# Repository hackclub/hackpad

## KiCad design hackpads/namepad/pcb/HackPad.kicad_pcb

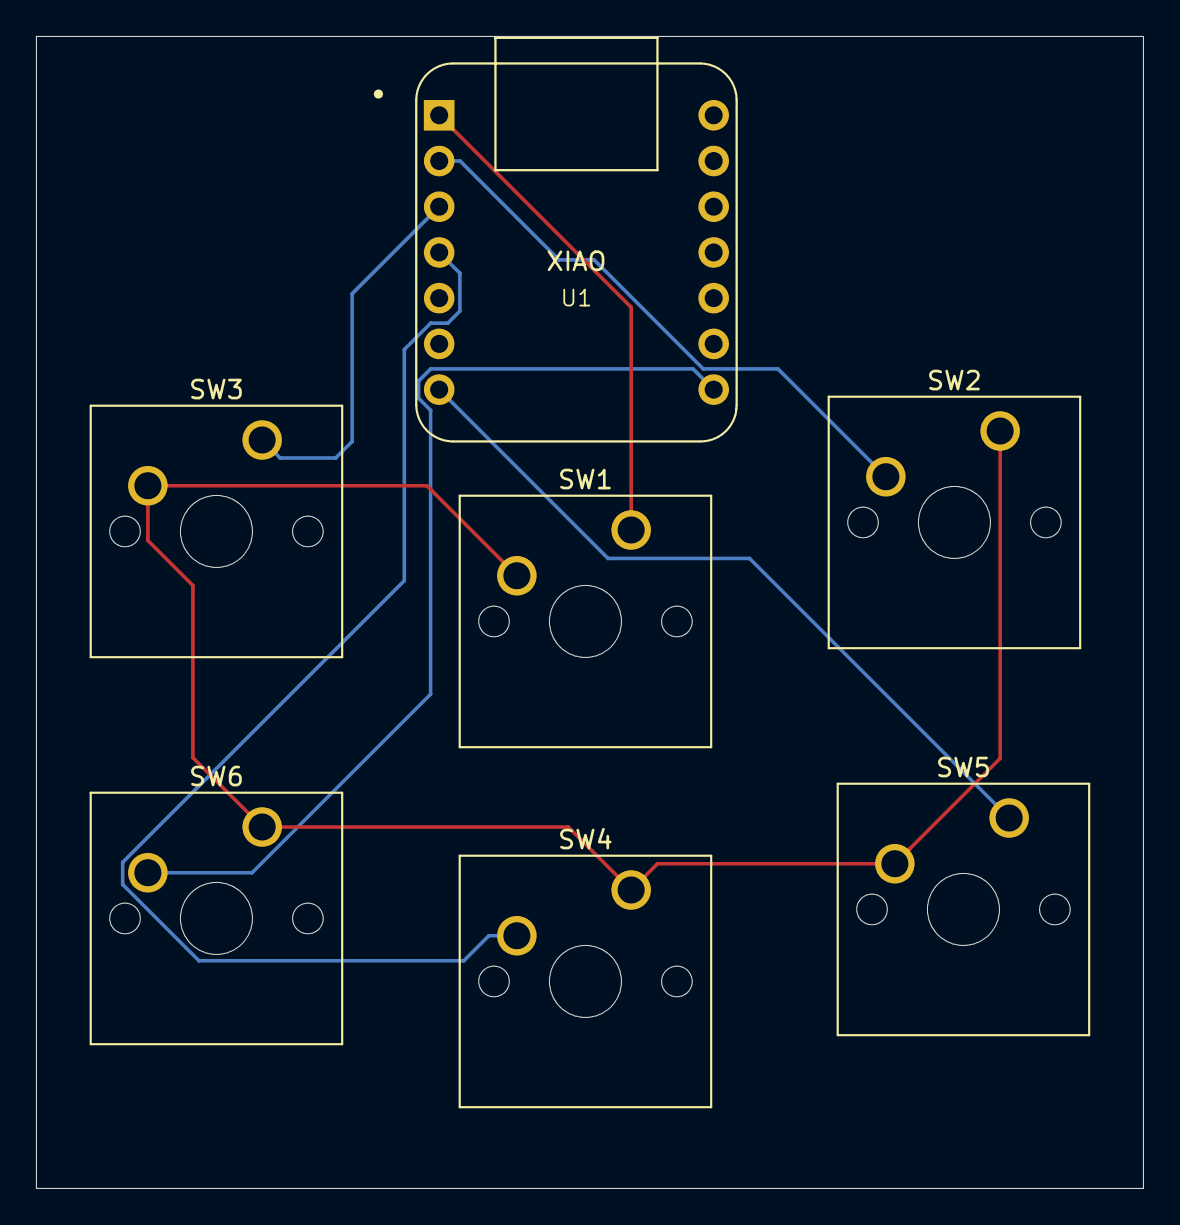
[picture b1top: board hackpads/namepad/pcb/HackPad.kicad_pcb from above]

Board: 2 copper layers, 61.5 x 64.0 mm, 7 parts (0 on the bottom side), 7 nets.

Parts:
SW1, SW2, SW3, SW4, SW5, SW6: SW_Push; SW_Cherry_MX_1.00u_PCB
U1: Seeed Studio XIAO SAMD21; XIAO-Generic-Thruhole-14P-2.54-21X17.8MM

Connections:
GND: SW1.2, SW2.1, SW3.2, SW4.1, SW5.2, SW6.1
SW1: SW1.1, U1.1 (PA02_A0_D0)
SW2: SW2.2, U1.2 (PA4_A1_D1)
SW3: SW3.1, U1.3 (PA10_A2_D2)
SW4: SW4.2, U1.4 (PA11_A3_D3)
SW5: SW5.1, U1.7 (PB08_A6_D6_TX)
SW6: SW6.2, U1.8 (PB09_A7_D7_RX)

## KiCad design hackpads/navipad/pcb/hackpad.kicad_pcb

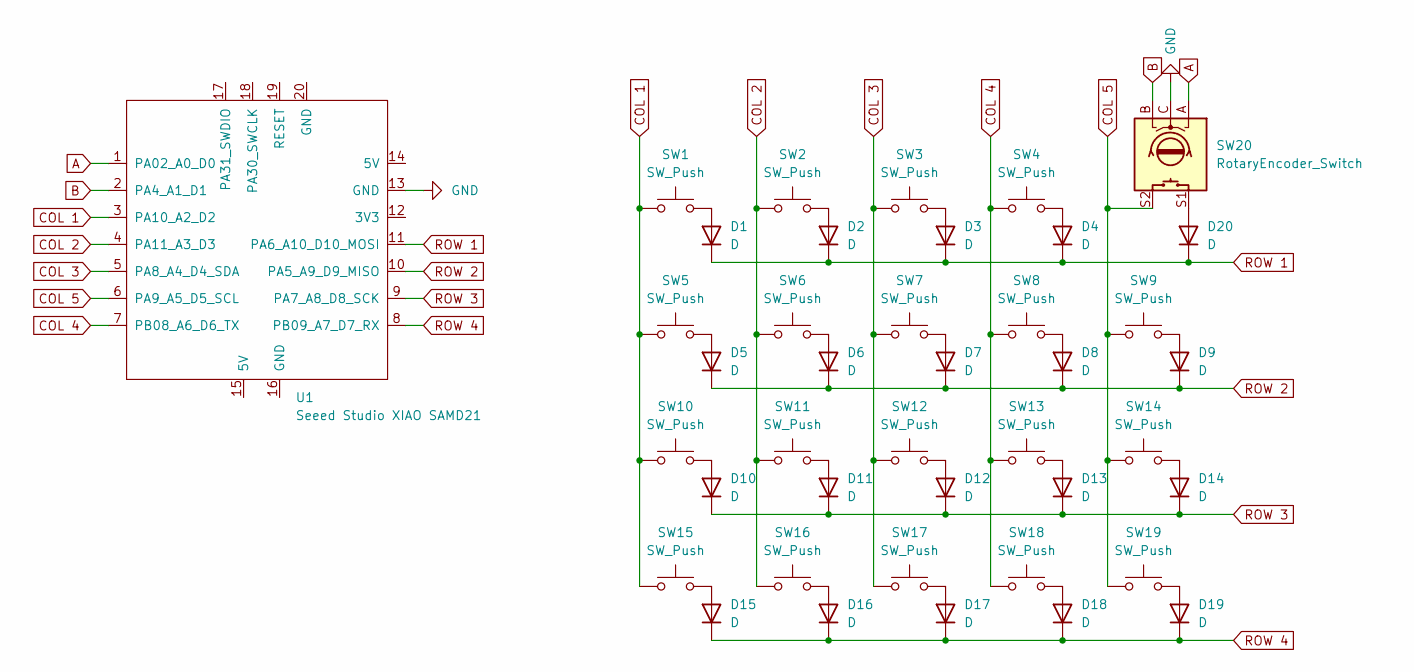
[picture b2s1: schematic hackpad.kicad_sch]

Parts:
D1, D2, D3, D4, D5, D6, D7, D8, D9, D10, D11, D12, D13, D14, D15, D16, D17, D18, D19, D20: D; D_DO-35_SOD27_P7.62mm_Horizontal
SW1, SW2, SW3, SW4, SW5, SW6, SW7, SW8, SW9, SW10, SW11, SW12, SW13, SW14, SW15, SW16, SW17, SW18, SW19: SW_Push; SW_Cherry_MX_1.00u_PCB_3D
SW20: RotaryEncoder_Switch; RotaryEncoder_Alps_EC11E-Switch_Vertical_H20mm_3D
U1: Seeed Studio XIAO SAMD21; XIAO-Generic-Thruhole-14P-2.54-21X17.8MM_3D

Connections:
A: SW20.A, U1.1 (PA02_A0_D0)
B: SW20.B, U1.2 (PA4_A1_D1)
COL 1: SW1.1, SW5.1, SW10.1, SW15.1, U1.3 (PA10_A2_D2)
COL 2: SW2.1, SW6.1, SW11.1, SW16.1, U1.4 (PA11_A3_D3)
COL 3: SW3.1, SW7.1, SW12.1, SW17.1, U1.5 (PA8_A4_D4_SDA)
COL 4: SW4.1, SW8.1, SW13.1, SW18.1, U1.7 (PB08_A6_D6_TX)
COL 5: SW9.1, SW14.1, SW19.1, SW20.S2, U1.6 (PA9_A5_D5_SCL)
GND: SW20.C, U1.13 (GND)
unnamed: D1.2 (A), SW1.2
unnamed: D2.2 (A), SW2.2
unnamed: D3.2 (A), SW3.2
unnamed: D4.2 (A), SW4.2
unnamed: D5.2 (A), SW5.2
unnamed: D6.2 (A), SW6.2
unnamed: D7.2 (A), SW7.2
unnamed: D8.2 (A), SW8.2
unnamed: D9.2 (A), SW9.2
unnamed: D10.2 (A), SW10.2
unnamed: D11.2 (A), SW11.2
unnamed: D12.2 (A), SW12.2
unnamed: D13.2 (A), SW13.2
unnamed: D14.2 (A), SW14.2
unnamed: D15.2 (A), SW15.2
unnamed: D16.2 (A), SW16.2
unnamed: D17.2 (A), SW17.2
unnamed: D18.2 (A), SW18.2
unnamed: D19.2 (A), SW19.2
unnamed: D20.2 (A), SW20.S1
ROW 1: D1.1 (K), D2.1 (K), D3.1 (K), D4.1 (K), D20.1 (K), U1.11 (PA6_A10_D10_MOSI)
ROW 2: D5.1 (K), D6.1 (K), D7.1 (K), D8.1 (K), D9.1 (K), U1.10 (PA5_A9_D9_MISO)
ROW 3: D10.1 (K), D11.1 (K), D12.1 (K), D13.1 (K), D14.1 (K), U1.9 (PA7_A8_D8_SCK)
ROW 4: D15.1 (K), D16.1 (K), D17.1 (K), D18.1 (K), D19.1 (K), U1.8 (PB09_A7_D7_RX)

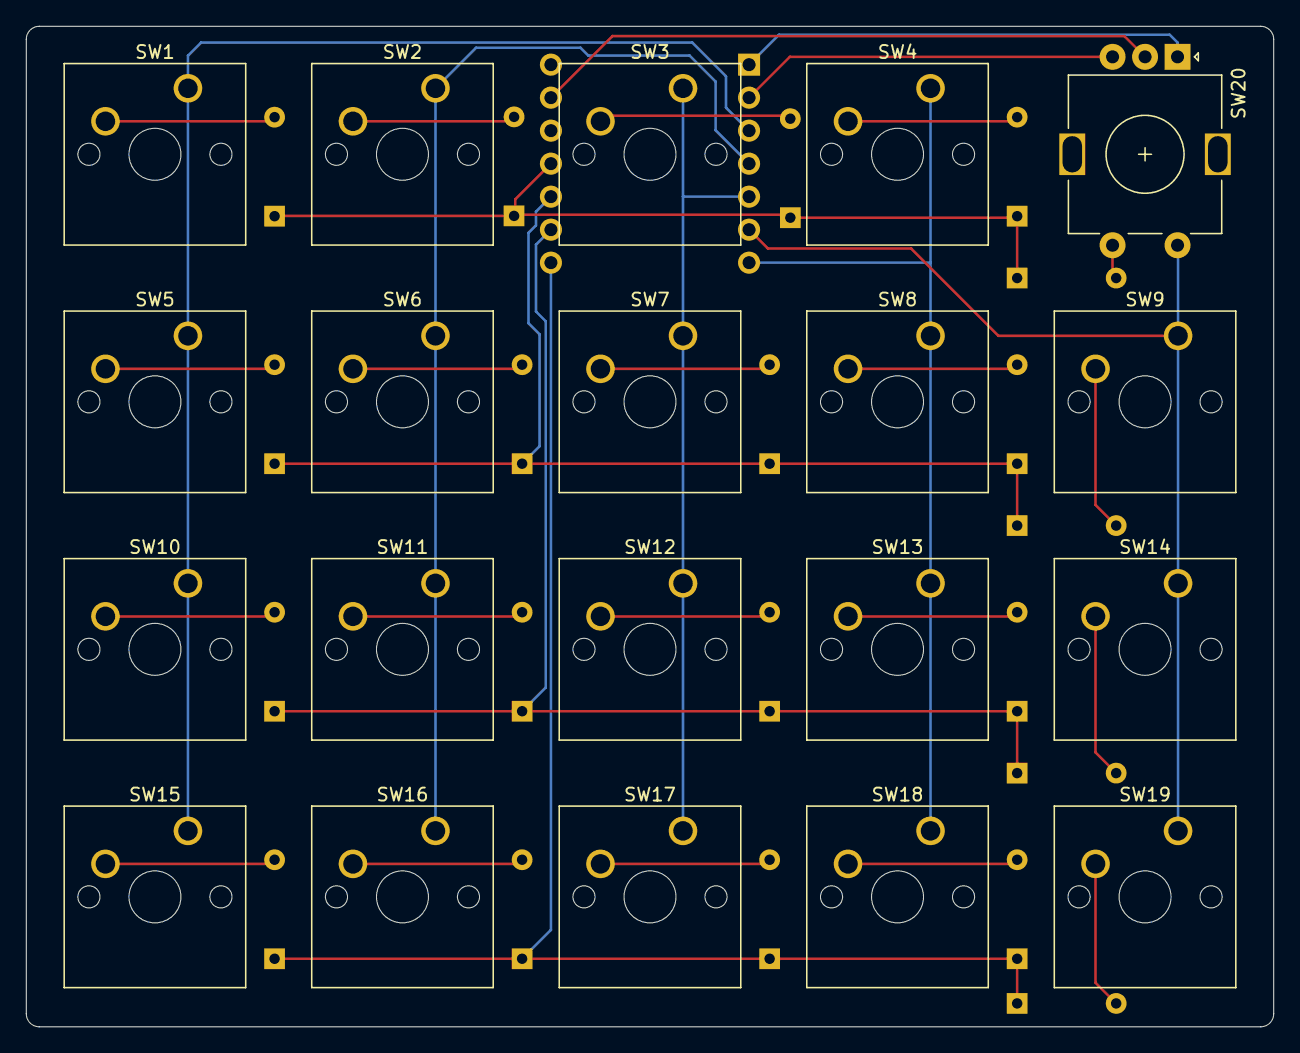
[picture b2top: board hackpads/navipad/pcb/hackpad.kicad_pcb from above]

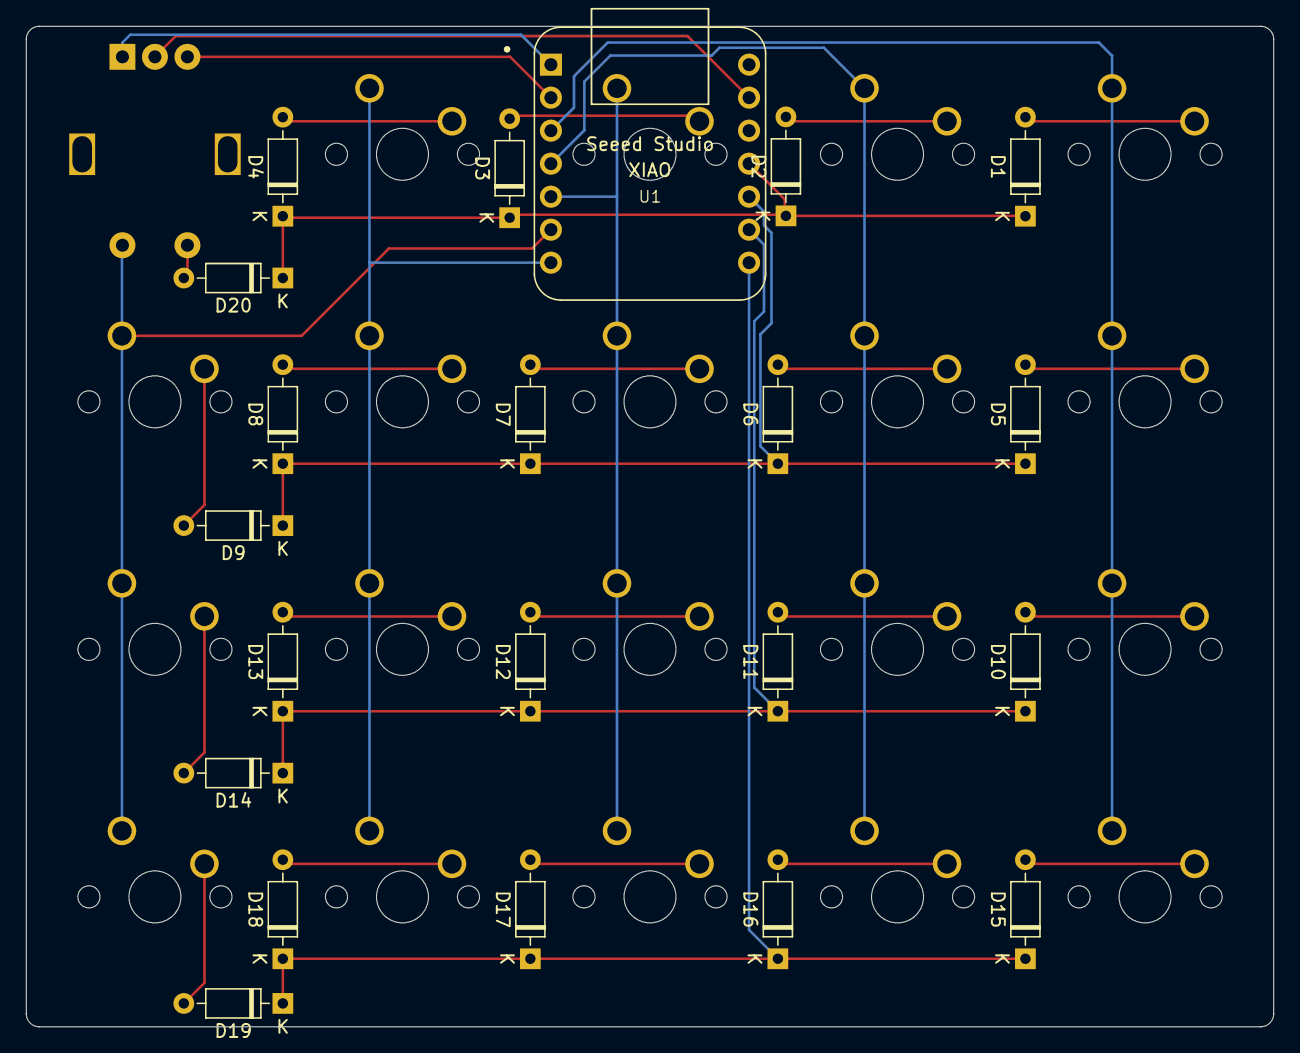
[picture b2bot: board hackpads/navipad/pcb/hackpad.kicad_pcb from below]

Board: 2 copper layers, 96.0 x 77.0 mm, 41 parts (21 on the bottom side), 32 nets.

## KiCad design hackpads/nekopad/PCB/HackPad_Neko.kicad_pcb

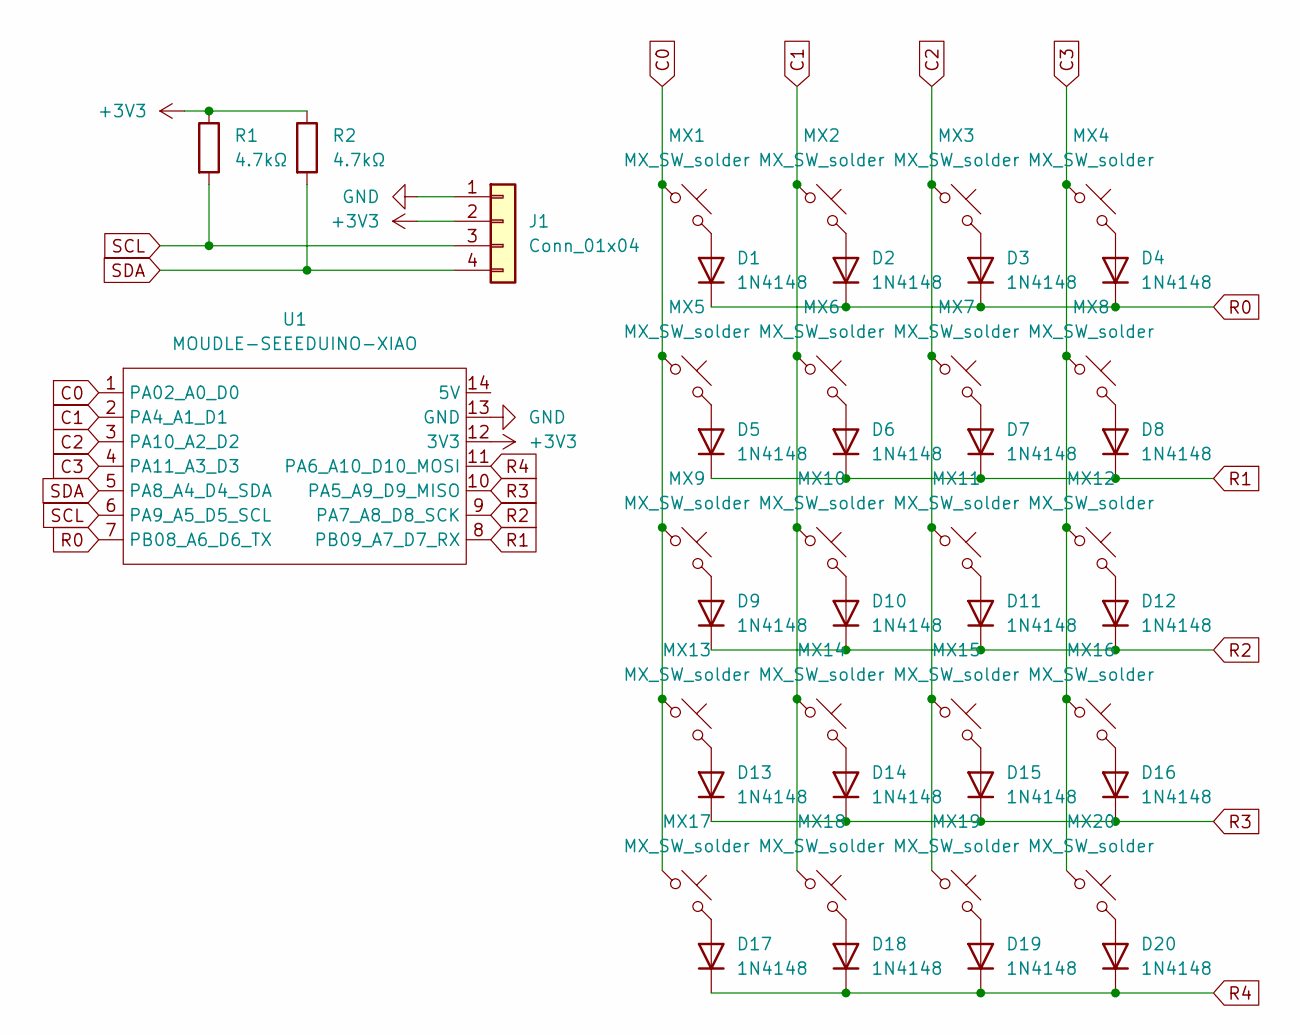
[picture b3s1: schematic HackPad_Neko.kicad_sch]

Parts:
D1, D2, D3, D4, D5, D6, D7, D8, D9, D10, D11, D12, D13, D14, D15, D16, D17, D18, D19, D20: 1N4148; D_DO-35_SOD27_P7.62mm_Horizontal
J1: Conn_01x04; SSD1306-0.91-OLED-4pin-128x32
MX1, MX2, MX3, MX4, MX5, MX6, MX7, MX8, MX9, MX10, MX11, MX12, MX13, MX14, MX15, MX16, MX17, MX18, MX19, MX20: MX_SW_solder; SW_Cherry_MX_1.00u_PCB
R1, R2: 4.7kΩ; R_Axial_DIN0204_L3.6mm_D1.6mm_P5.08mm_Horizontal
U1: MOUDLE-SEEEDUINO-XIAO; MOUDLE14P-2.54-21X17.8MM

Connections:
+3V3: J1.2, R1.1, R2.1, U1.12 (3V3)
C0: MX1.1, MX5.1, MX9.1, MX13.1, MX17.1, U1.1 (PA02_A0_D0)
C1: MX2.1, MX6.1, MX10.1, MX14.1, MX18.1, U1.2 (PA4_A1_D1)
C2: MX3.1, MX7.1, MX11.1, MX15.1, MX19.1, U1.3 (PA10_A2_D2)
C3: MX4.1, MX8.1, MX12.1, MX16.1, MX20.1, U1.4 (PA11_A3_D3)
GND: J1.1, U1.13 (GND)
unnamed: D1.2 (A), MX1.2
unnamed: D2.2 (A), MX2.2
unnamed: D3.2 (A), MX3.2
unnamed: D4.2 (A), MX4.2
unnamed: D5.2 (A), MX5.2
unnamed: D6.2 (A), MX6.2
unnamed: D7.2 (A), MX7.2
unnamed: D8.2 (A), MX8.2
unnamed: D9.2 (A), MX9.2
unnamed: D10.2 (A), MX10.2
unnamed: D11.2 (A), MX11.2
unnamed: D12.2 (A), MX12.2
unnamed: D13.2 (A), MX13.2
unnamed: D14.2 (A), MX14.2
unnamed: D15.2 (A), MX15.2
unnamed: D16.2 (A), MX16.2
unnamed: D17.2 (A), MX17.2
unnamed: D18.2 (A), MX18.2
unnamed: D19.2 (A), MX19.2
unnamed: D20.2 (A), MX20.2
R0: D1.1 (K), D2.1 (K), D3.1 (K), D4.1 (K), U1.7 (PB08_A6_D6_TX)
R1: D5.1 (K), D6.1 (K), D7.1 (K), D8.1 (K), U1.8 (PB09_A7_D7_RX)
R2: D9.1 (K), D10.1 (K), D11.1 (K), D12.1 (K), U1.9 (PA7_A8_D8_SCK)
R3: D13.1 (K), D14.1 (K), D15.1 (K), D16.1 (K), U1.10 (PA5_A9_D9_MISO)
R4: D17.1 (K), D18.1 (K), D19.1 (K), D20.1 (K), U1.11 (PA6_A10_D10_MOSI)
SCL: J1.3, R1.2, U1.6 (PA9_A5_D5_SCL)
SDA: J1.4, R2.2, U1.5 (PA8_A4_D4_SDA)

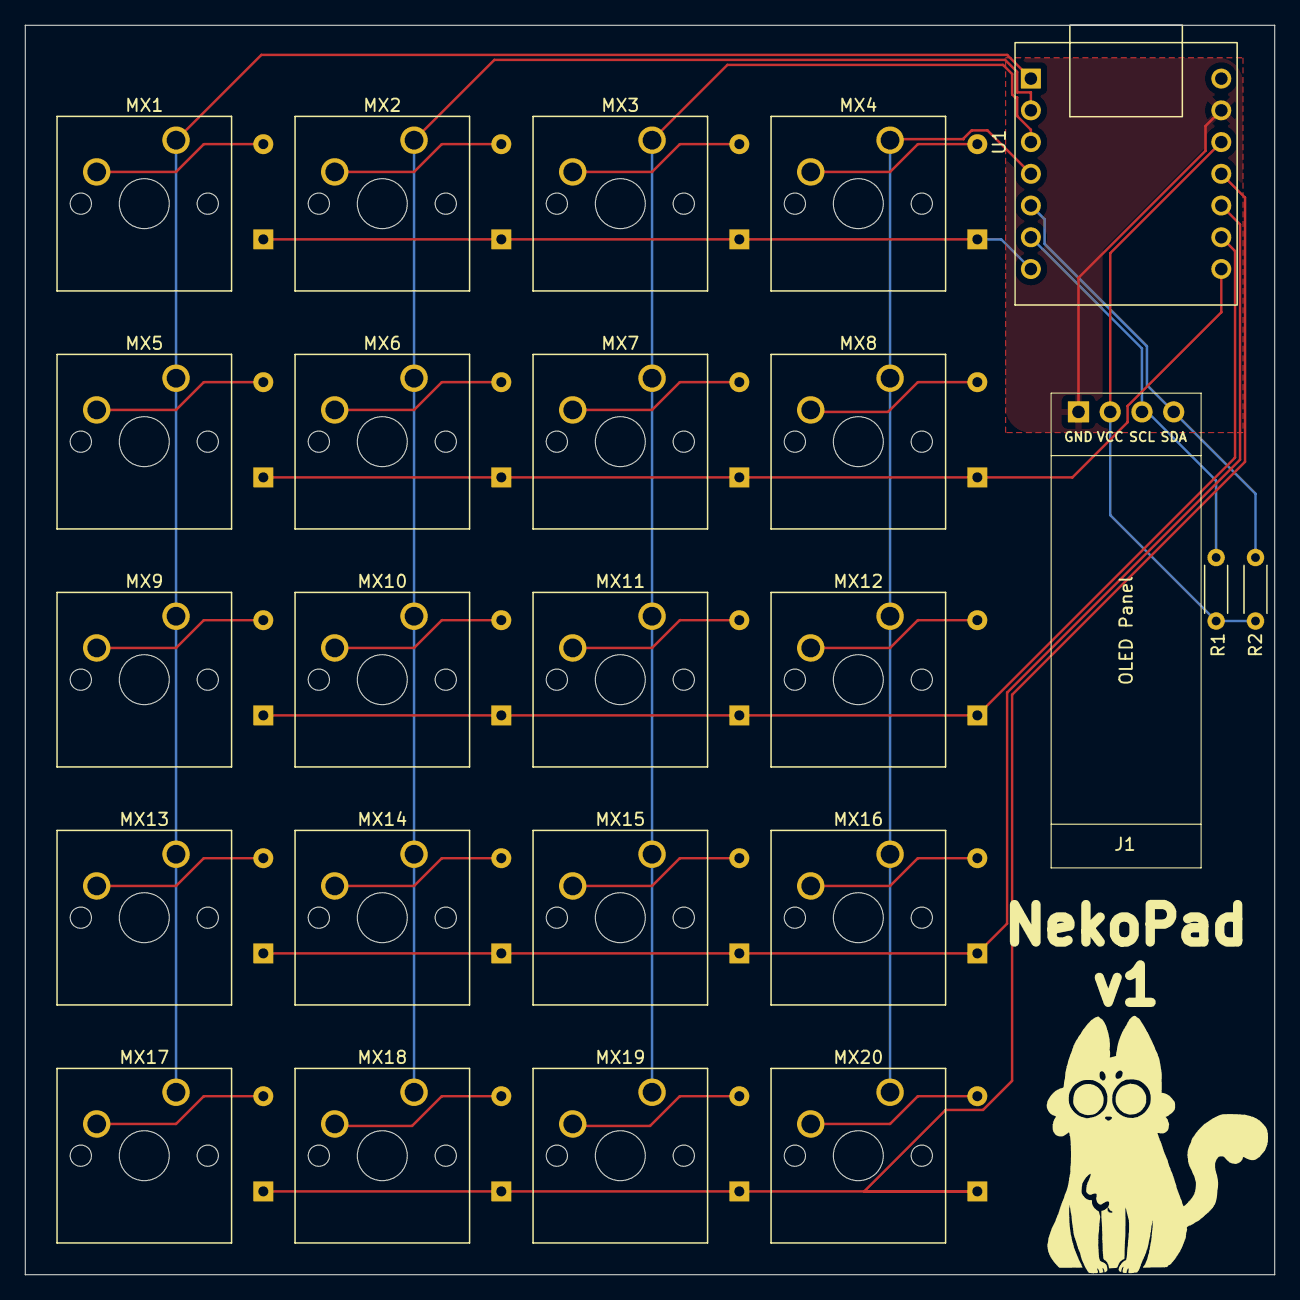
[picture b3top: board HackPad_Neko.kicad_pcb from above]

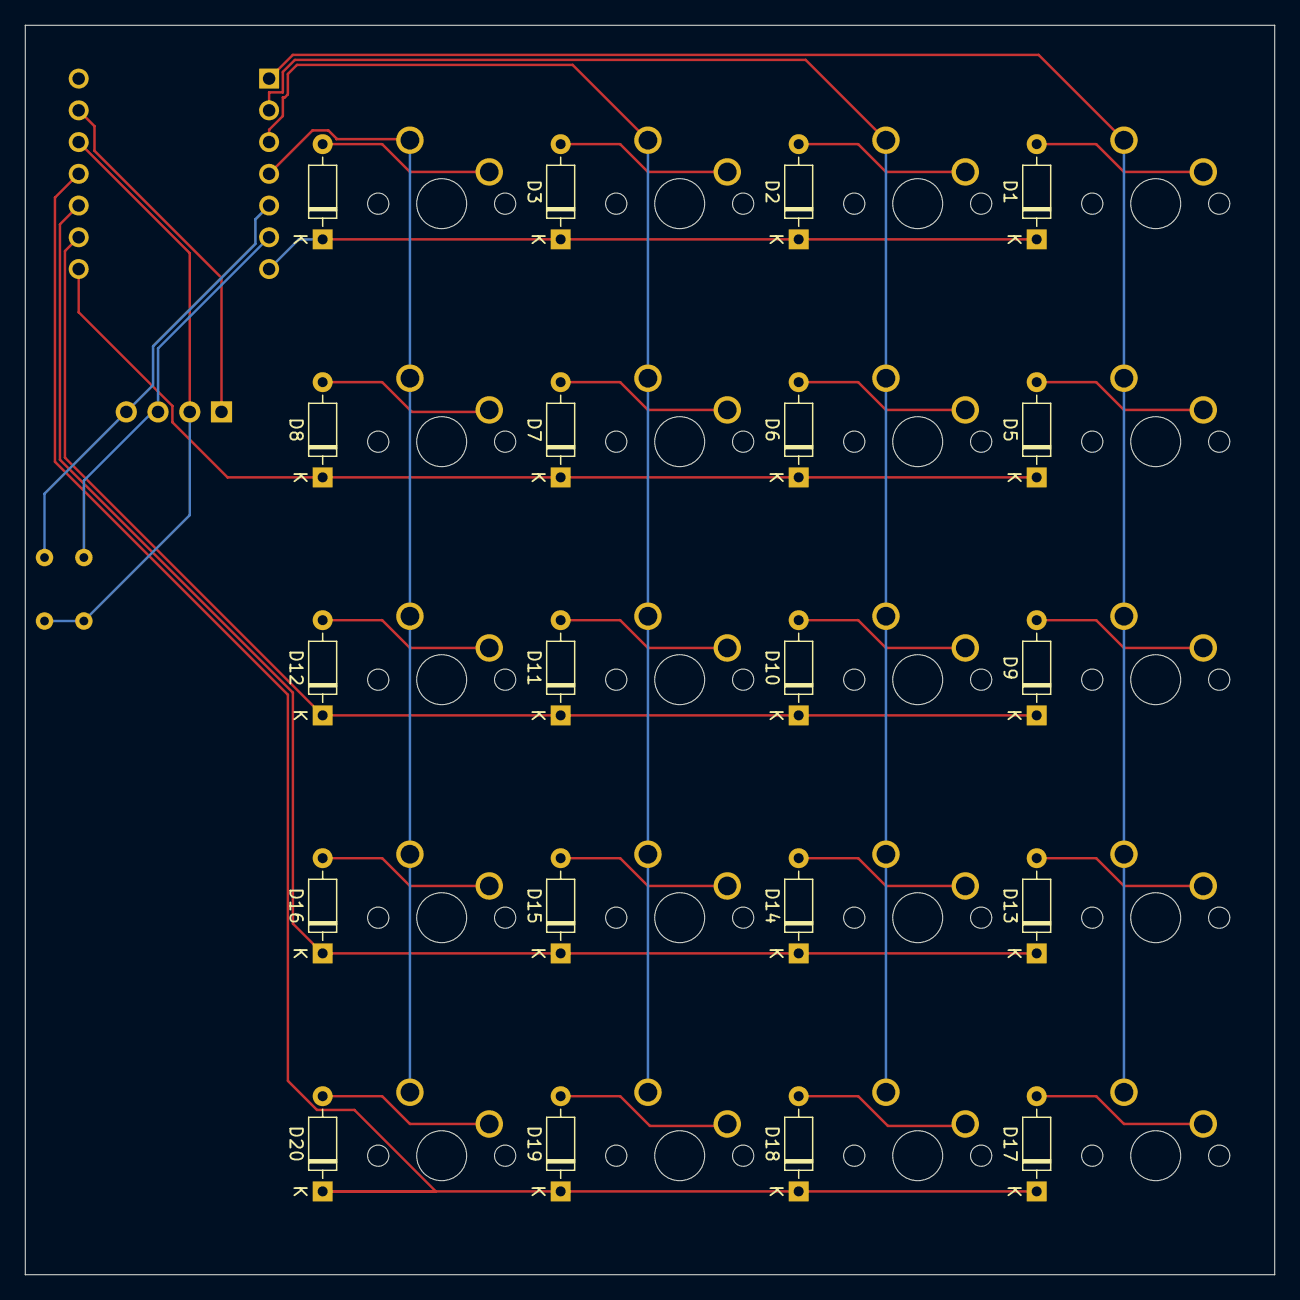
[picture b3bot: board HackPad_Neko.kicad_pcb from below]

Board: 2 copper layers, 100.0 x 100.0 mm, 44 parts (20 on the bottom side), 33 nets.

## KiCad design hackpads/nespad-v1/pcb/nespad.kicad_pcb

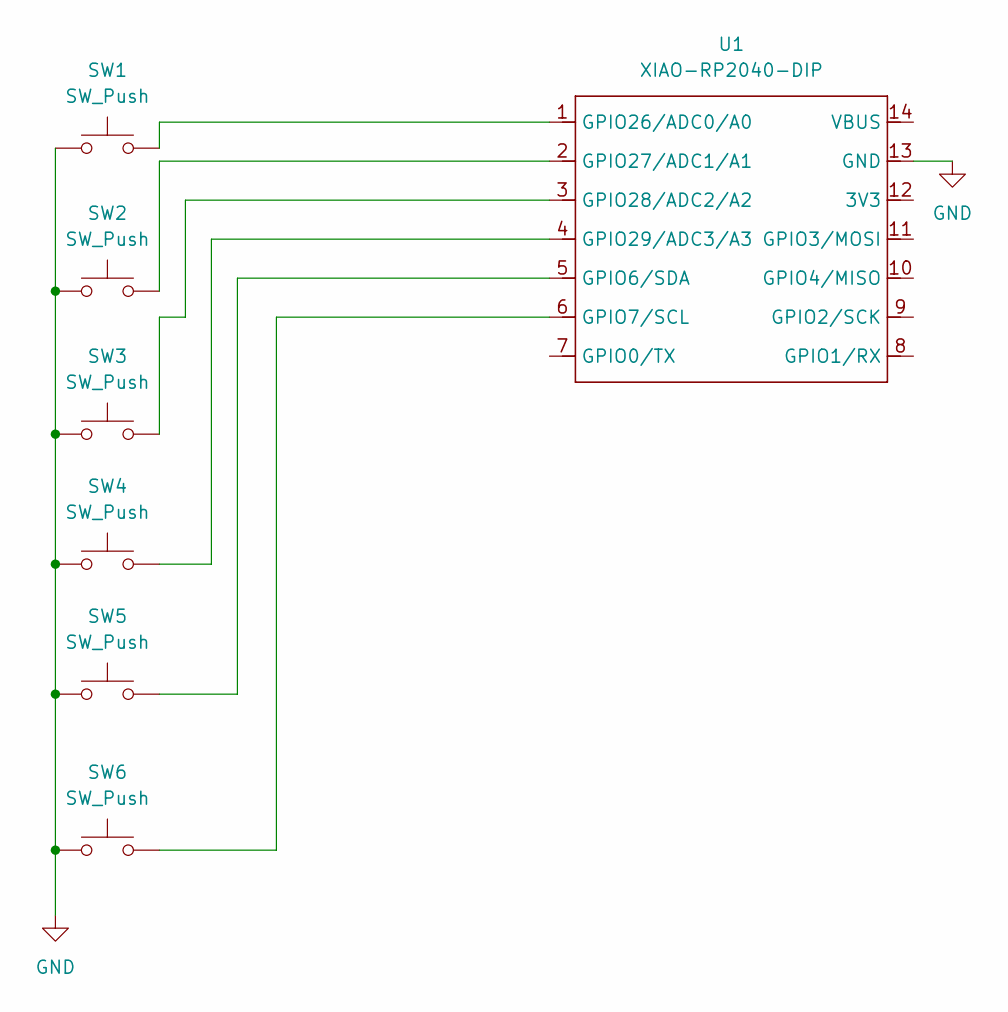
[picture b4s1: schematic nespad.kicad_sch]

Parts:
SW1, SW2, SW3, SW4, SW5, SW6: SW_Push; SW_Cherry_MX_1.00u_PCB
U1: XIAO-RP2040-DIP

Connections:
GND: SW1.1, SW2.1, SW3.1, SW4.1, SW5.1, SW6.1, U1.13 (GND)
unnamed: SW5.2, U1.5 (GPIO6/SDA)
unnamed: SW6.2, U1.6 (GPIO7/SCL)
unnamed: SW1.2, U1.1 (GPIO26/ADC0/A0)
unnamed: SW2.2, U1.2 (GPIO27/ADC1/A1)
unnamed: SW3.2, U1.3 (GPIO28/ADC2/A2)
unnamed: SW4.2, U1.4 (GPIO29/ADC3/A3)

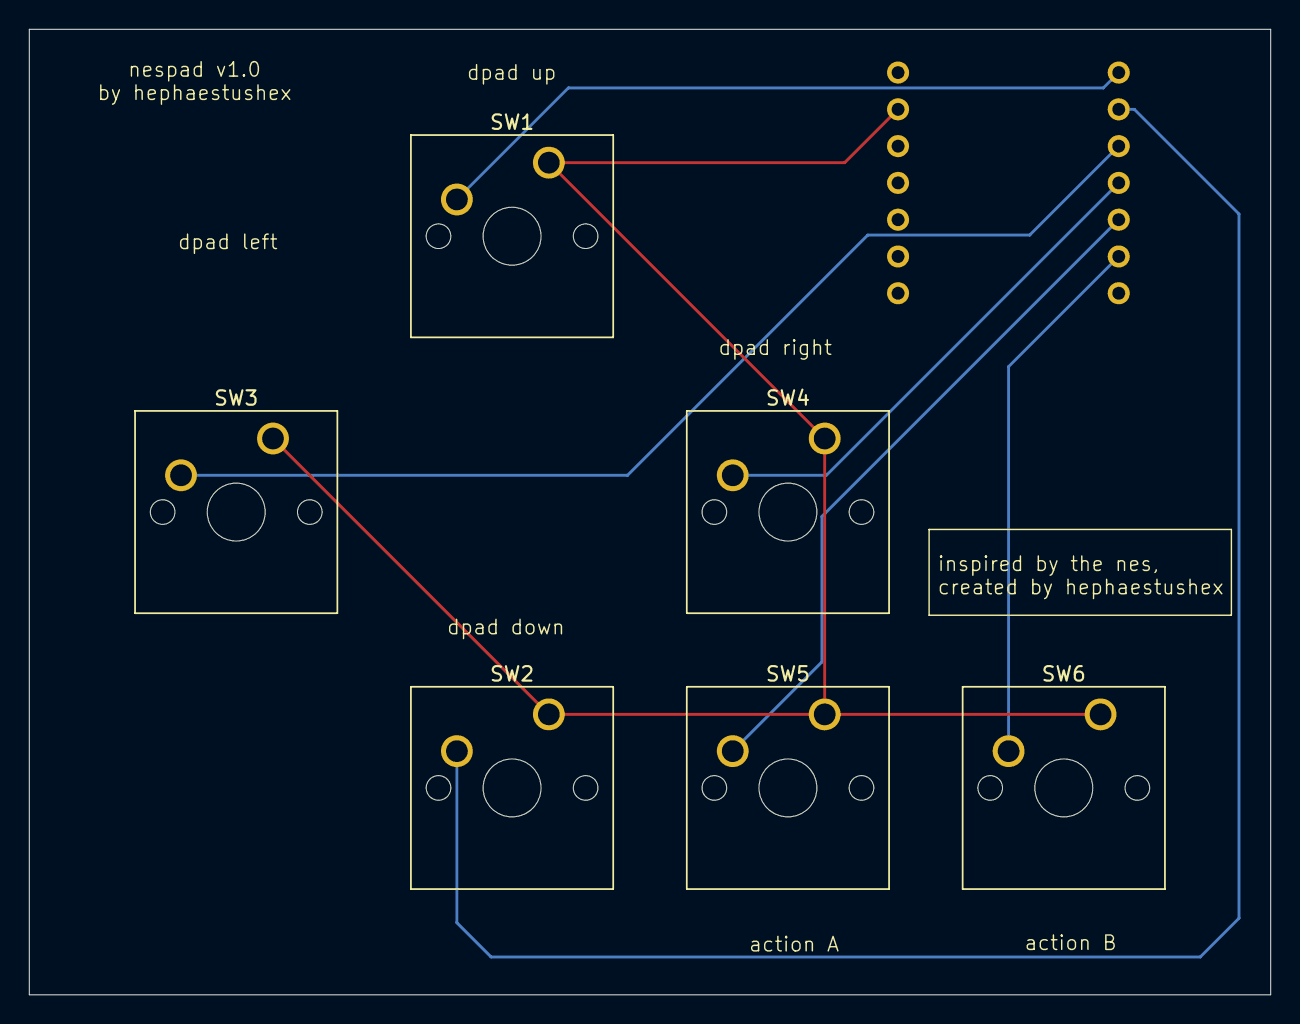
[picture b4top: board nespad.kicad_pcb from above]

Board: 2 copper layers, 85.7 x 66.7 mm, 7 parts (1 on the bottom side), 7 nets.

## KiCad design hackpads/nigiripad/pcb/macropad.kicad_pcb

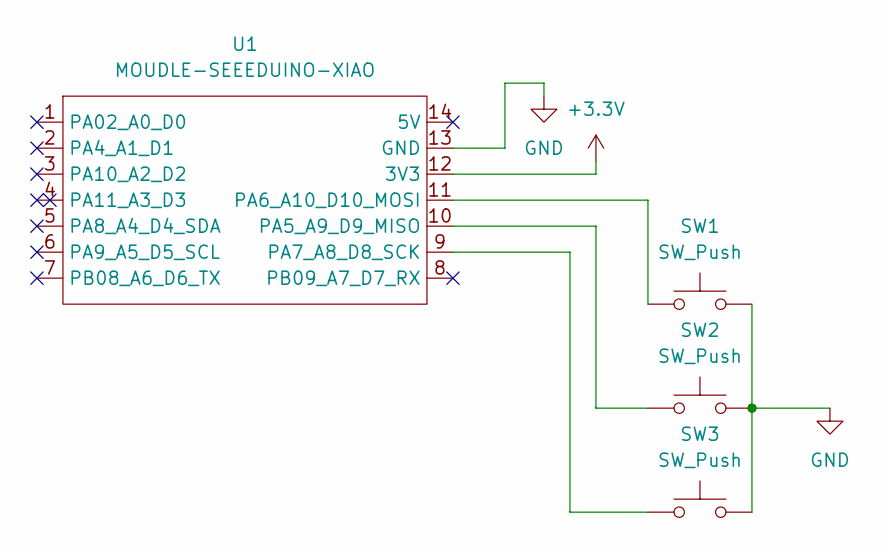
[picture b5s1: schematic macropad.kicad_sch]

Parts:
SW1, SW2, SW3: SW_Push; SW_Cherry_MX_1.00u_PCB
U1: MOUDLE-SEEEDUINO-XIAO; XIAO-Generic-Hybrid-14P-2.54-21X17.8MM

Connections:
+3.3V: U1.12 (3V3)
GND: SW1.2, SW2.2, SW3.2, U1.13 (GND)
unnamed: SW2.1, U1.10 (PA5_A9_D9_MISO)
unnamed: SW1.1, U1.11 (PA6_A10_D10_MOSI)
unnamed: SW3.1, U1.9 (PA7_A8_D8_SCK)

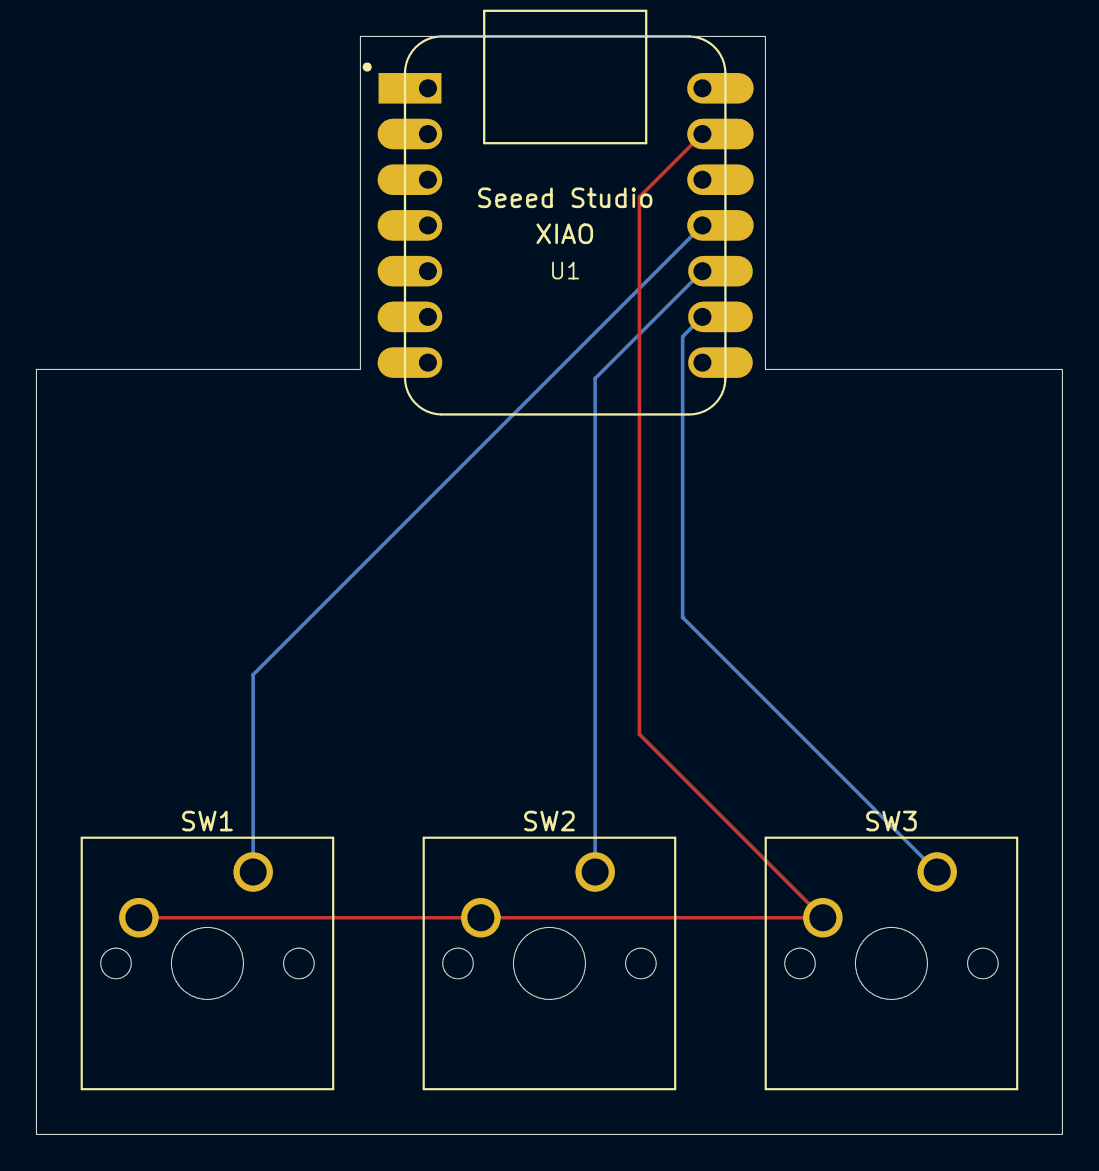
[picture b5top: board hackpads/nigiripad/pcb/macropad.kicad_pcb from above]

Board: 2 copper layers, 57.0 x 61.0 mm, 4 parts (0 on the bottom side), 4 nets.

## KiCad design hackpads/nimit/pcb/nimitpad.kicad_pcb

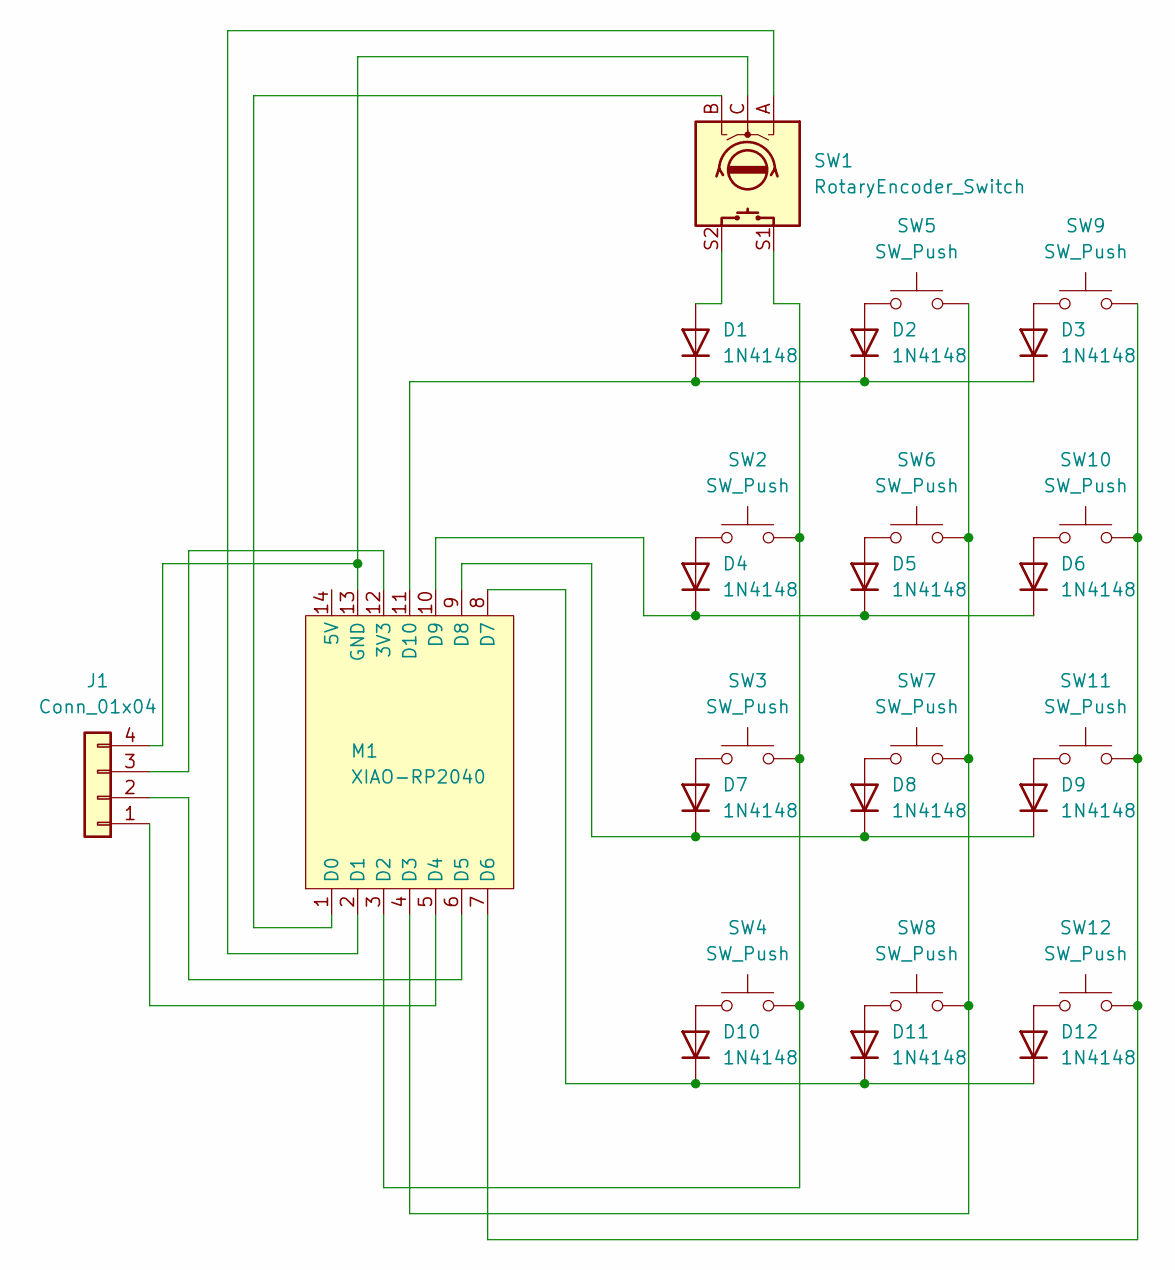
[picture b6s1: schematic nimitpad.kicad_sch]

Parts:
D1, D2, D3, D4, D5, D6, D7, D8, D9, D10, D11, D12: 1N4148; D_DO-35_SOD27_P7.62mm_Horizontal
J1: Conn_01x04; 128x64OLED
M1: XIAO-RP2040
SW1: RotaryEncoder_Switch; RotaryEncoder_Alps_EC11E-Switch_Vertical_H20mm
SW2, SW3, SW4, SW5, SW6, SW7, SW8, SW9, SW10, SW11, SW12: SW_Push; MX_PCB_1.00u

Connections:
unnamed: D1.2 (A), SW1.S2
unnamed: D1.1 (K), D2.1 (K), D3.1 (K), M1.11 (D10)
unnamed: D2.2 (A), SW5.1
unnamed: D3.2 (A), SW9.1
unnamed: D4.2 (A), SW2.1
unnamed: D4.1 (K), D5.1 (K), D6.1 (K), M1.10 (D9)
unnamed: D5.2 (A), SW6.1
unnamed: D6.2 (A), SW10.1
unnamed: D7.2 (A), SW3.1
unnamed: D7.1 (K), D8.1 (K), D9.1 (K), M1.9 (D8)
unnamed: D8.2 (A), SW7.1
unnamed: D9.2 (A), SW11.1
unnamed: D10.2 (A), SW4.1
unnamed: D10.1 (K), D11.1 (K), D12.1 (K), M1.8 (D7)
unnamed: D11.2 (A), SW8.1
unnamed: D12.2 (A), SW12.1
unnamed: J1.1, M1.5 (D4)
unnamed: J1.2, M1.6 (D5)
unnamed: J1.3, M1.12 (3V3)
unnamed: J1.4, M1.13 (GND), SW1.C
unnamed: M1.1 (D0), SW1.B
unnamed: M1.2 (D1), SW1.A
unnamed: M1.3 (D2), SW1.S1, SW2.2, SW3.2, SW4.2
unnamed: M1.4 (D3), SW5.2, SW6.2, SW7.2, SW8.2
unnamed: M1.7 (D6), SW9.2, SW10.2, SW11.2, SW12.2

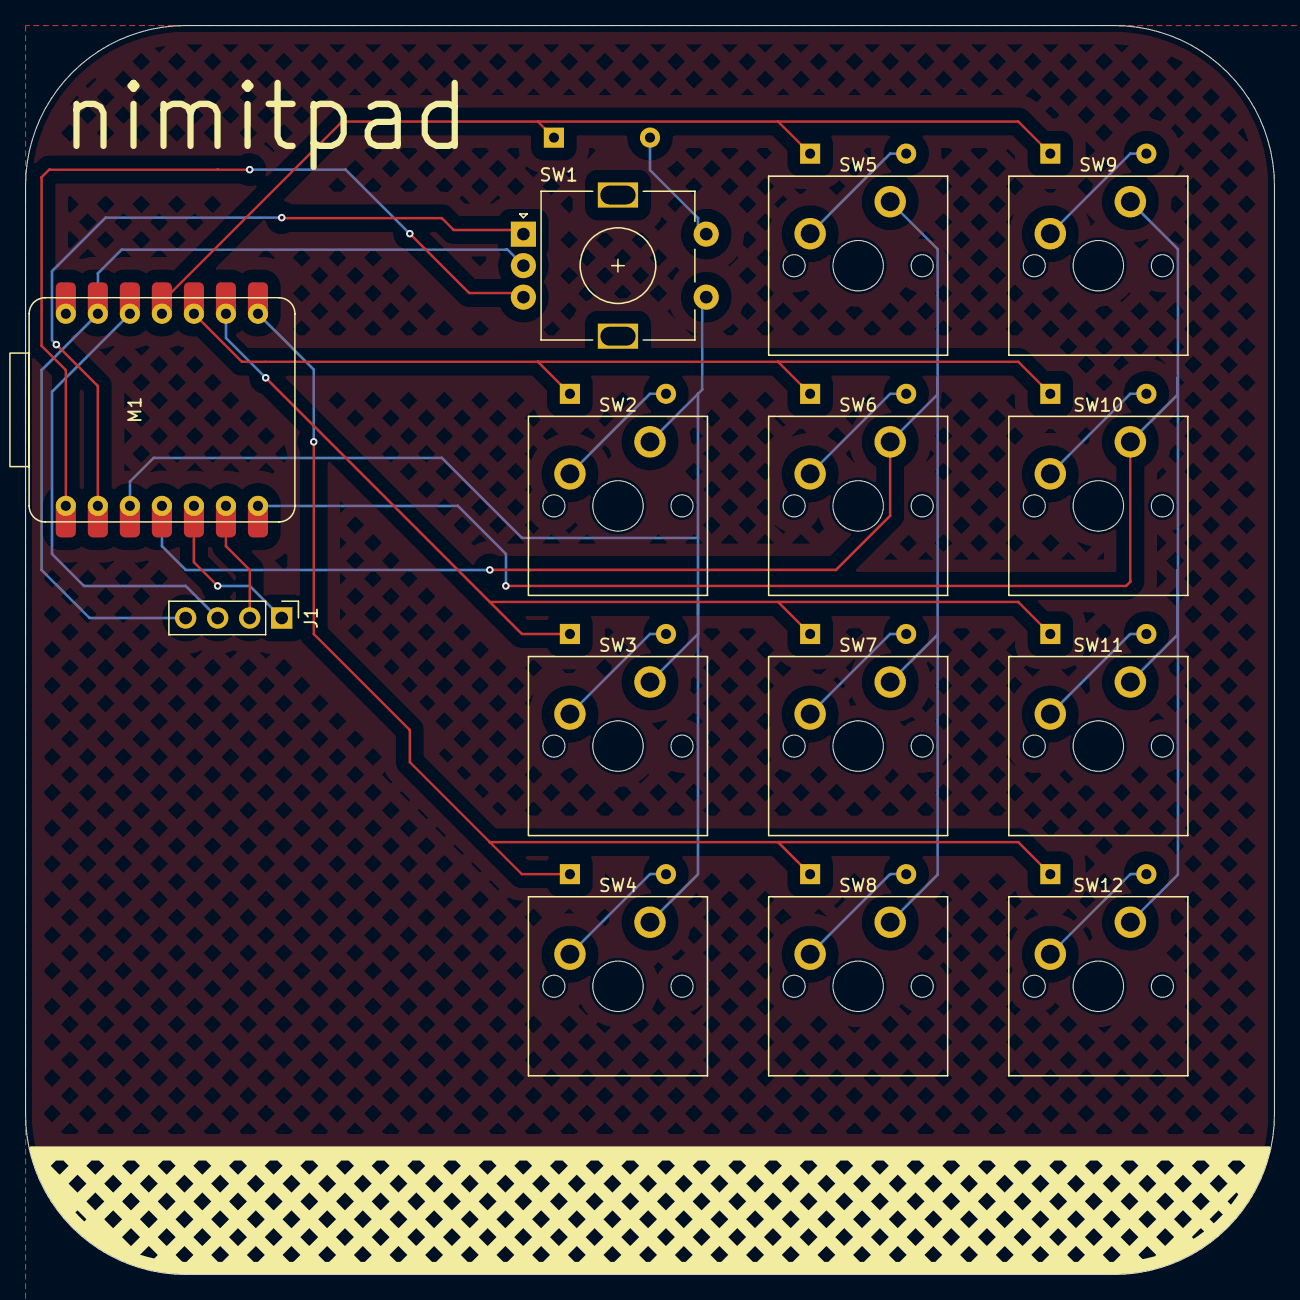
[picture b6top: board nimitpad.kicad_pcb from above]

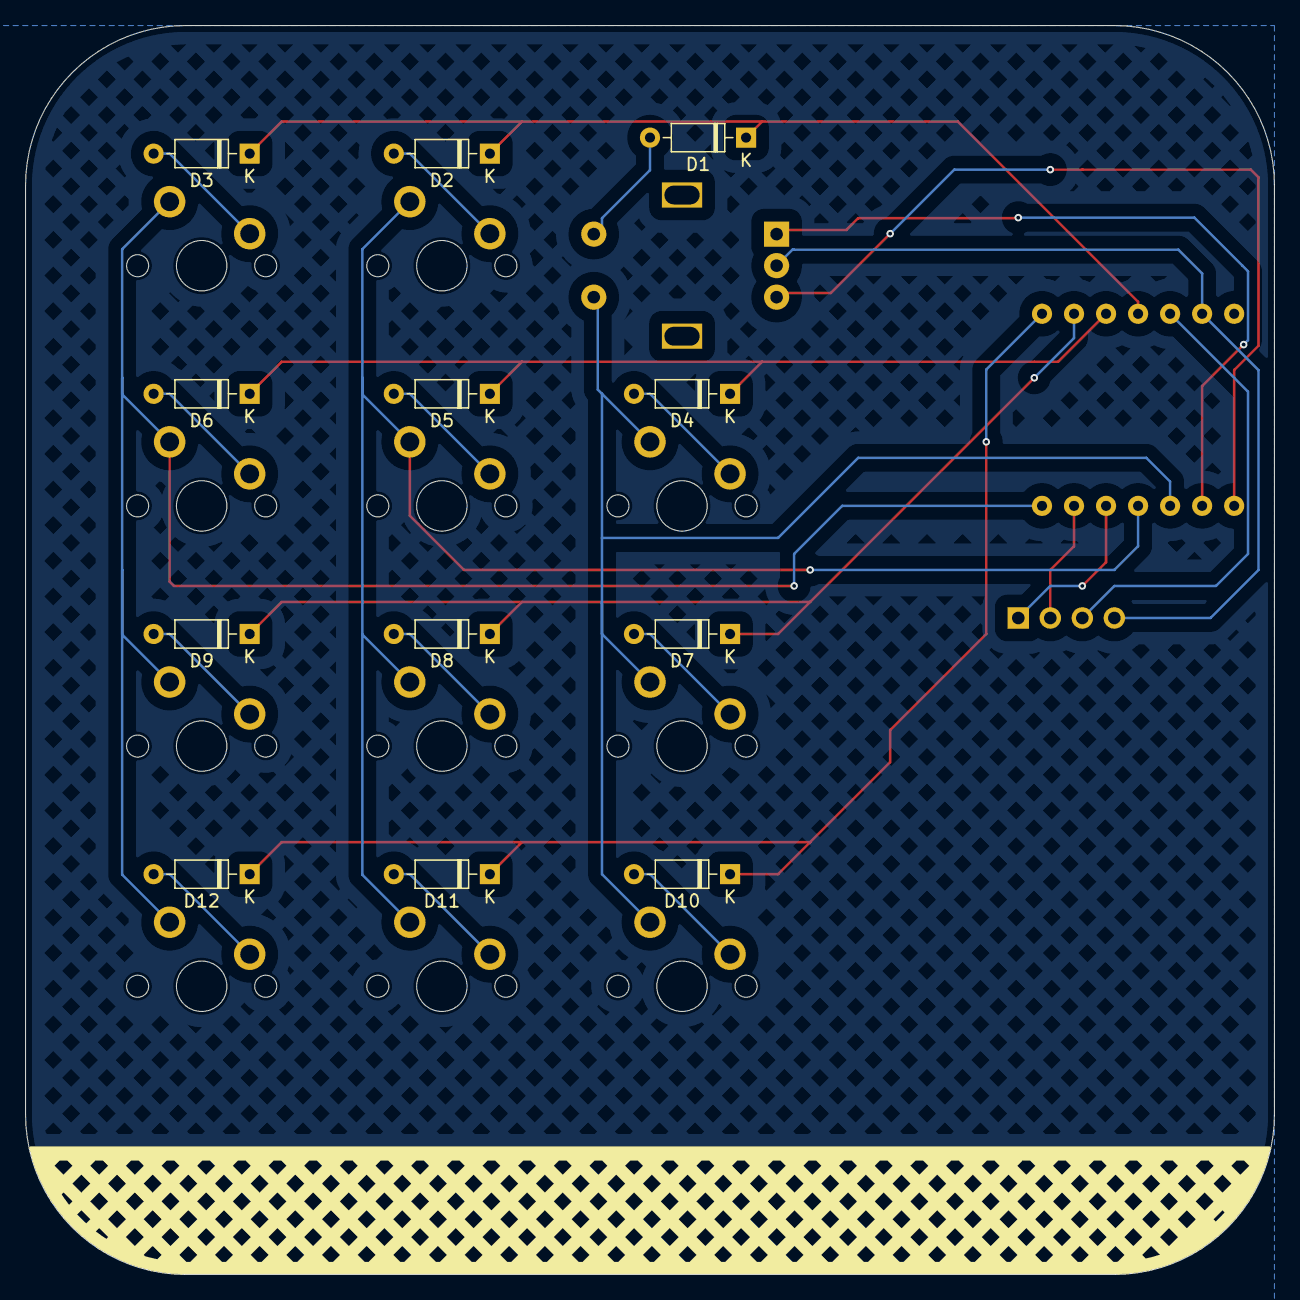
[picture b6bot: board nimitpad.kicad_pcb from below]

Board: 11 copper layers, 99.1 x 99.1 mm, 26 parts (12 on the bottom side), 25 nets.
